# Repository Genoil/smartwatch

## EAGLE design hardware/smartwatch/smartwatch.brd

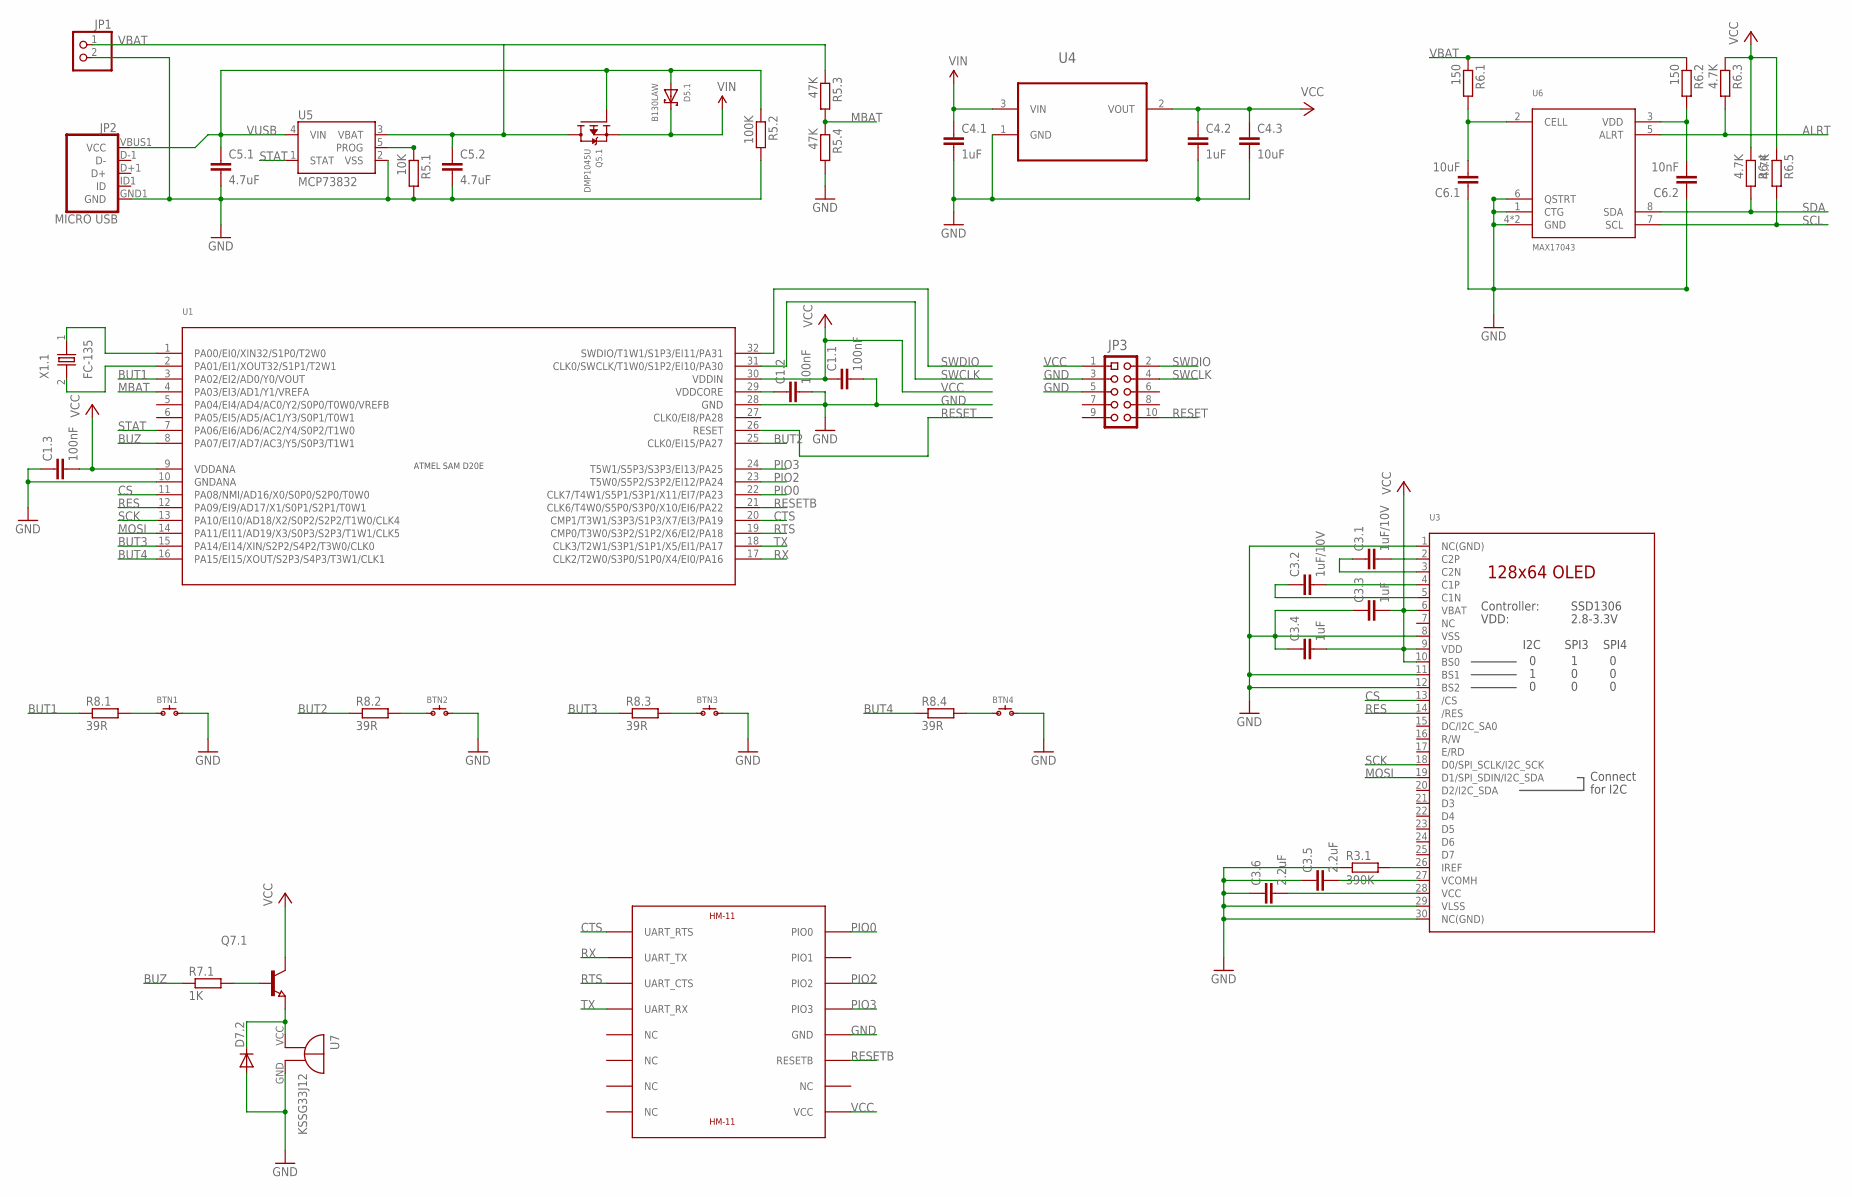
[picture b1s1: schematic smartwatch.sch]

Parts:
BTN1, BTN2, BTN3, BTN4: SPST.B3U-3000P(M); B3U-3000P(M)
C1.1, C1.2, C1.3: 100nF; C0805
C3.1, C3.2: 1uF/10V; C0805
C3.3, C3.4, C4.1, C4.2: 1uF; C0805
C3.5, C3.6: 2.2uF; C0805
C4.3, C6.1: 10uF; C0805
C5.1, C5.2: 4.7uF; C0805
C6.2: 10nF; C0805
D5.1: B130LAW; SOD-123
D7.2: CGRM4001-G; SOD-123_MINI-SMA
JP1: PINHD-1X2; 1X02
JP2: MICRO USB; USB-B-MICRO-SMD_V03
JP3: PF2X5SMD1.27MM; PF2X5SMD50MIL
Q5.1: DMP1045U; SOT23-R
Q7.1: NPN-TRANSISTOR_SOT23; SOT23
R3.1: 390K; R2012
R5.1: 10K; R2012
R5.2: 100K; R2012
R5.3, R5.4: 47K; R2012
R6.1, R6.2: 150; R2012
R6.3, R6.4, R6.5: 4.7K; R2012
R7.1: 1K; R2012
R8.1, R8.2, R8.3, R8.4: 39R; R2012
U1: SAMD20E; TQFP32-08
U2: HM-11
U3: DISP_OLED_UG-2864HSWEG010.96"; UG-2864HSWEG01_0.96IN_WRAPAROUND
U4: MCP1700T-3302E/TT; SOT95P237X112-3N
U5: MCP73832; SOT23-5
U6: MAX17043; 8-TDFN-EP
U7: KSSG33J12
X1.1: FC-135

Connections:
ALRT: R6.3.2, U6.5 (ALRT)
BUT1: R8.1.1, U1.3 (PA02/EI2/AD0/Y0/VOUT)
BUT2: R8.2.1, U1.25 (CLK0/EI15/PA27)
BUT3: R8.3.1, U1.15 (PA14/EI14/XIN/S2P2/S4P2/T3W0/CLK0)
BUT4: R8.4.1, U1.16 (PA15/EI15/XOUT/S2P3/S4P3/T3W1/CLK1)
BUZ: R7.1.1, U1.8 (PA07/EI7/AD7/AC3/Y5/S0P3/T1W1)
CS: U1.11 (PA08/NMI/AD16/X0/S0P0/S2P0/T0W0), U3.13 (/CS)
CTS: U1.20 (CMP1/T3W1/S3P3/S1P3/X7/EI3/PA19), U2.UART_RTS
GND: BTN1.2, BTN2.2, BTN3.2, BTN4.2, C1.1.2, C1.2.2, C1.3.1, C3.3.1, C3.4.1, C3.5.1, C3.6.1, C4.1.2, C4.2.2, C4.3.2, C5.1.2, C5.2.2, C6.1.1, C6.2.1, D7.2.A, JP1.2, JP2.GND1 (GND), JP3.3, JP3.5, R3.1.1, R5.1.2, R5.2.2, R5.4.2, U1.10 (GNDANA), U1.28 (GND), U2.GND, U3.1 (NC(GND)), U3.8 (VSS), U3.11 (BS1), U3.12 (BS2), U3.29 (VLSS), U3.30 (NC(GND)), U4.1 (GND), U5.2 (VSS), U6.1 (CTG), U6.4 (GND), U6.6 (QSTRT), U6.9 (GND), U7.GND (-)
MBAT: R5.3.2, R5.4.1, U1.4 (PA03/EI3/AD1/Y1/VREFA)
MOSI: U1.14 (PA11/EI11/AD19/X3/S0P3/S2P3/T1W1/CLK5), U3.19 (D1/SPI_SDIN/I2C_SDA)
unnamed: C3.1.2, U3.2 (C2P)
unnamed: C3.1.1, U3.3 (C2N)
unnamed: C3.2.2, U3.4 (C1P)
unnamed: C3.2.1, U3.5 (C1N)
unnamed: R3.1.2, U3.26 (IREF)
unnamed: C3.5.2, U3.27 (VCOMH)
unnamed: C3.6.2, U3.28 (VCC)
unnamed: BTN1.1, R8.1.2
unnamed: U1.1 (PA00/EI0/XIN32/S1P0/T2W0), X1.1.1
unnamed: U1.2 (PA01/EI1/XOUT32/S1P1/T2W1), X1.1.2
unnamed: D7.2.C, Q7.1.2 (E), U7.VCC (+)
unnamed: Q7.1.1 (B), R7.1.2
unnamed: BTN2.1, R8.2.2
unnamed: C6.2.2, R6.2.2, U6.3 (VDD)
unnamed: BTN3.1, R8.3.2
unnamed: BTN4.1, R8.4.2
unnamed: C6.1.2, R6.1.2, U6.2 (CELL)
PIO0: U1.22 (CLK7/T4W1/S5P1/S3P1/X11/EI7/PA23), U2.PIO0
PIO2: U1.23 (T5W0/S5P2/S3P2/EI12/PA24), U2.PIO2
PIO3: U1.24 (T5W1/S5P3/S3P3/EI13/PA25), U2.PIO3
PROG: R5.1.1, U5.5 (PROG)
RES: U1.12 (PA09/EI9/AD17/X1/S0P1/S2P1/T0W1), U3.14 (/RES)
RESET: JP3.10, U1.26 (RESET)
RESETB: U1.21 (CLK6/T4W0/S5P0/S3P0/X10/EI6/PA22), U2.RESETB
RTS: U1.19 (CMP0/T3W0/S3P2/S1P2/X6/EI2/PA18), U2.UART_CTS
RX: U1.17 (CLK2/T2W0/S3P0/S1P0/X4/EI0/PA16), U2.UART_TX
SCK: U1.13 (PA10/EI10/AD18/X2/S0P2/S2P2/T1W0/CLK4), U3.18 (D0/SPI_SCLK/I2C_SCK)
SCL: R6.5.2, U6.7 (SCL)
SDA: R6.4.2, U6.8 (SDA)
STAT: U1.7 (PA06/EI6/AD6/AC2/Y4/S0P2/T1W0), U5.1 (STAT)
SWCLK: JP3.4, U1.31 (CLK0/SWCLK/T1W0/S1P2/EI10/PA30)
SWDIO: JP3.2, U1.32 (SWDIO/T1W1/S1P3/EI11/PA31)
TX: U1.18 (CLK3/T2W1/S3P1/S1P1/X5/EI1/PA17), U2.UART_RX
VBAT: C5.2.1, JP1.1, Q5.1.3 (D), R5.3.1, R6.1.1, R6.2.1, U5.3 (VBAT)
VCC: C1.1.1, C1.3.2, C3.3.2, C3.4.2, C4.2.1, C4.3.1, JP3.1, Q7.1.3 (C), R6.3.1, R6.4.1, R6.5.1, U1.9 (VDDANA), U1.30 (VDDIN), U2.VCC, U3.6 (VBAT), U3.9 (VDD), U3.10 (BS0), U4.2 (VOUT)
VDDCORE: C1.2.1, U1.29 (VDDCORE)
VIN: C4.1.1, D5.1.C, Q5.1.2 (S), U4.3 (VIN)
VUSB: C5.1.1, D5.1.A, JP2.VBUS1 (VCC), Q5.1.1 (G), R5.2.1, U5.4 (VIN)

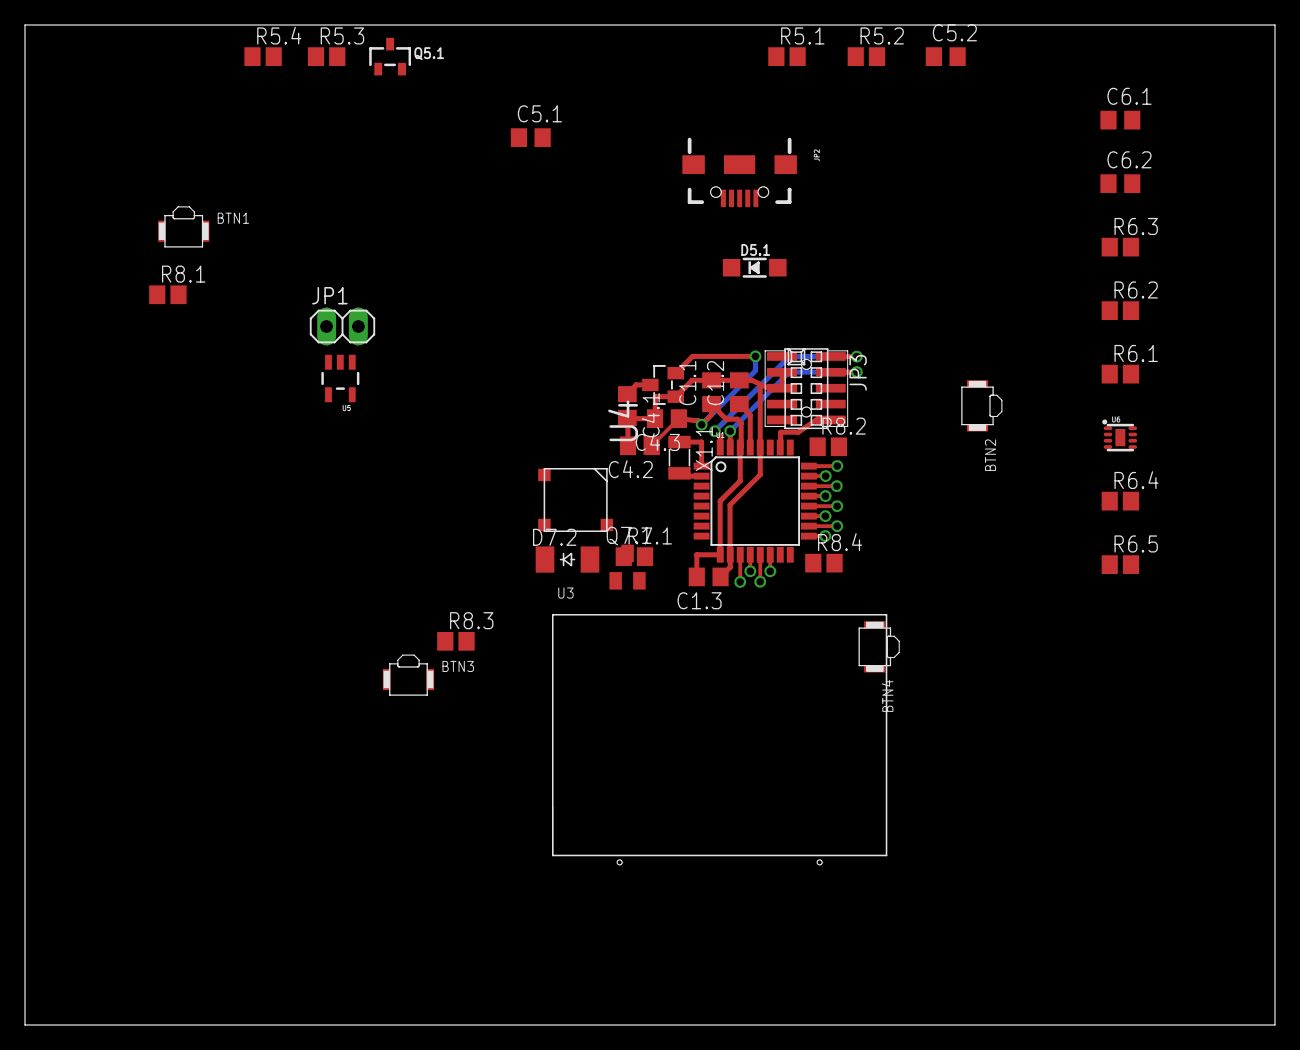
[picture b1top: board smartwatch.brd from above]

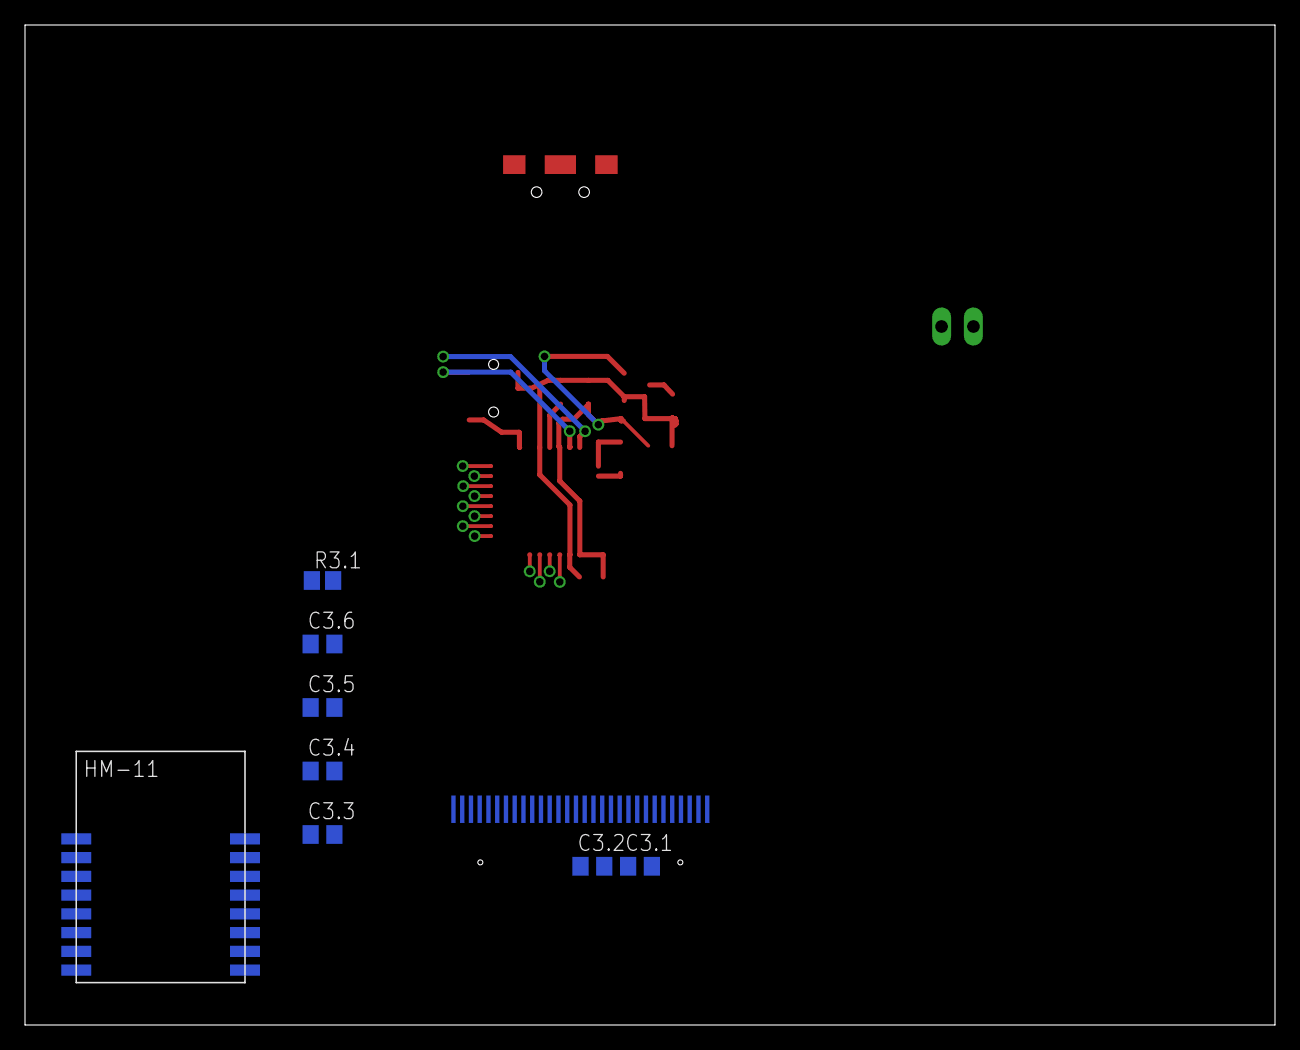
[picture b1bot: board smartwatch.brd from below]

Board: 2 copper layers, 100.0 x 80.0 mm, 50 parts (8 on the bottom side), 49 nets.

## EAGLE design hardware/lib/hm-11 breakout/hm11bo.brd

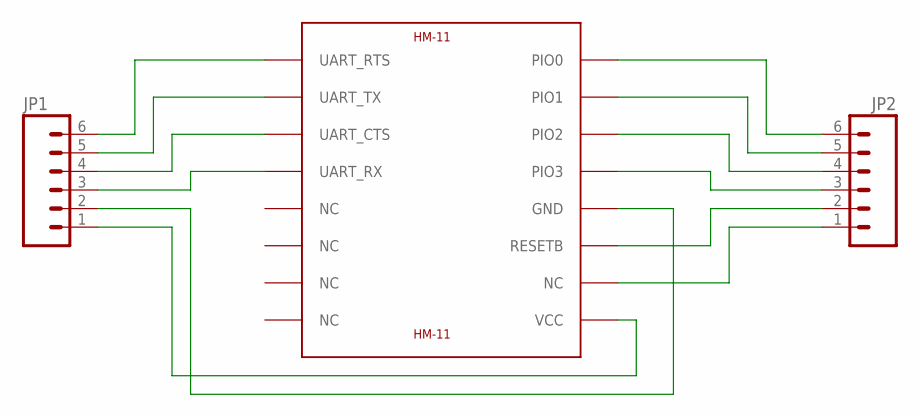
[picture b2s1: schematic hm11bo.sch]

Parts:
JP1, JP2: M06SIP; 1X06
U$1: HM-11

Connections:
CTS: JP1.4, U$1.UART_CTS
GND: JP1.2, U$1.GND
NC: JP2.1, U$1.NC@10 (NC)
PIO0: JP2.6, U$1.PIO0
PIO1: JP2.5, U$1.PIO1
PIO2: JP2.4, U$1.PIO2
PIO3: JP2.3, U$1.PIO3
RESETB: JP2.2, U$1.RESETB
RTS: JP1.6, U$1.UART_RTS
RX: JP1.3, U$1.UART_RX
TX: JP1.5, U$1.UART_TX
VCC: JP1.1, U$1.VCC

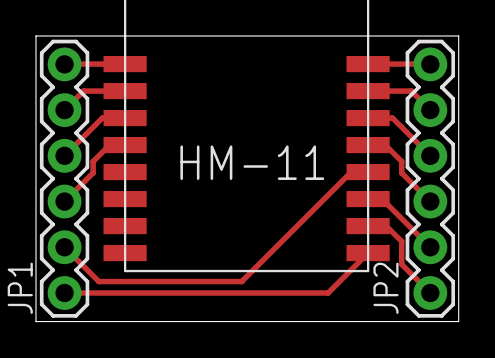
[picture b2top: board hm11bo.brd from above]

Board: 4 copper layers, 23.5 x 15.9 mm, 3 parts (0 on the bottom side), 12 nets.

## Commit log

2014-04-10 -initial commit after GDocs failure
2014-04-11 aded omron lib
2014-04-11 redid brd
2014-07-03 add brd
2019-03-16 README.md

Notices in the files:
parts and their libraries:
SparkFun-Connectors: Licensing: Creative Commons ShareAlike 4.0 International - https://creativecommons.org/licenses/by-sa/4.0
m-pad-2.1: License : GNU General Public License version 2 (see bottom)
